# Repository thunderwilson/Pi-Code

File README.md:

prog_draft is a basic implementation of bluetooth scanning and data logging.

Takes a mock daily roster "daily.csv" (as per TANDA rostering) and works out who is working today.

It takes note of their start time and end time for use in the scanning algorithm (hence why the daily.csv only has the first 4 colums, the rest are ignored).

Currently the program just scans for everyone in the list at once and logs the changes in state in the corresponding *name*.csv file rather than using the start and finish times to decide when to scan. Thats this weeks job.

This file is then stored locally ready to be uploaded.

Currently using the bluetooth address of my phone and two fake addresses for testing. Only the Tom.csv file shows actual test data. Have ordered parts for the Bluetooth 'smart' badges which should arrive sometime next week. 

Running code on linux laptop which is setup the same as the Rasperry Pi (the Pi is not very powerful and would be a bitch to develop on).

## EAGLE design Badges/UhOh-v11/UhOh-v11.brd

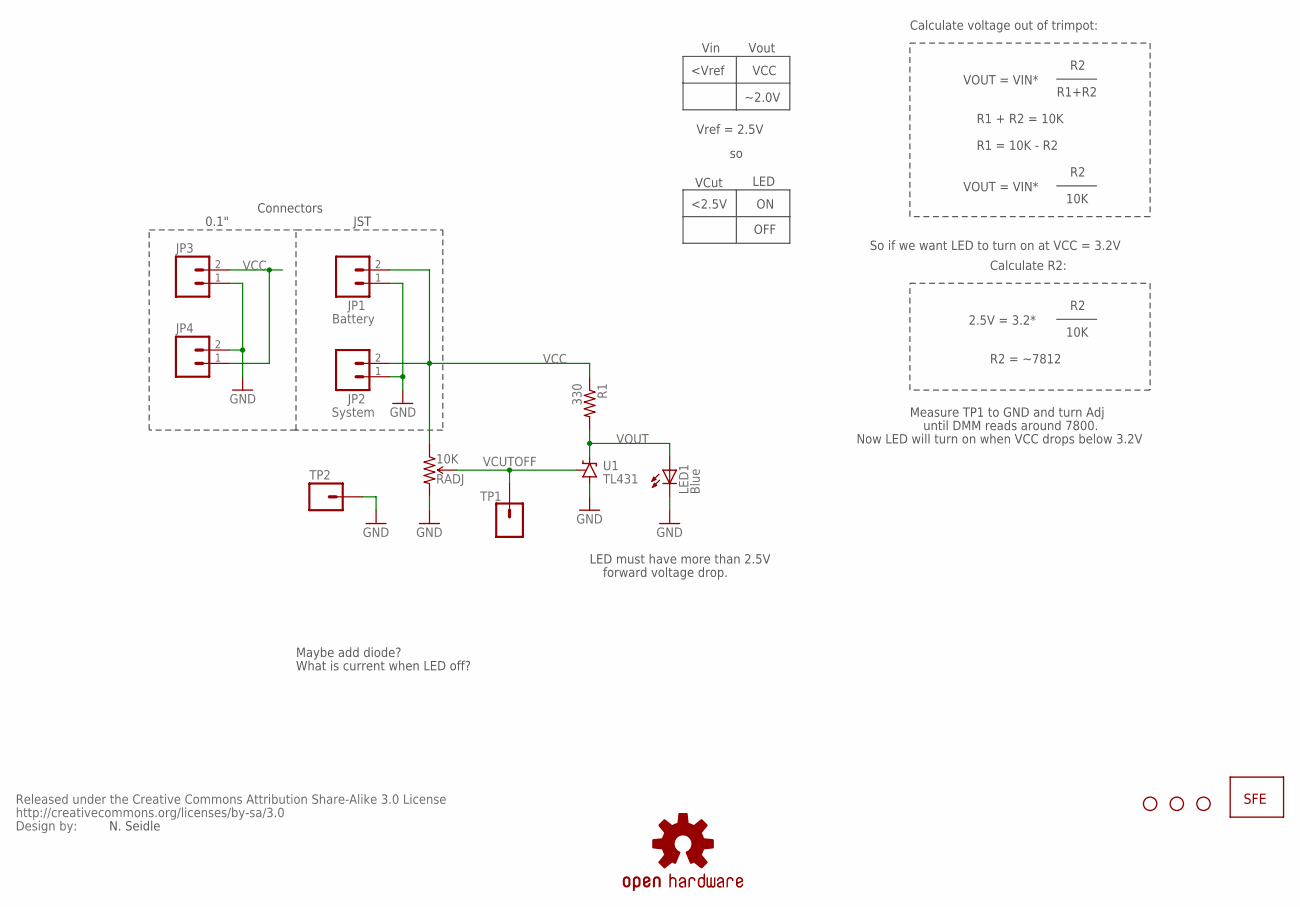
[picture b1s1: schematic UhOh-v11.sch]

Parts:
JP1: Battery; JST-2-PTH
JP2: System; JST-2-PTH
JP3, JP4: M02PTH; 1X02
JP31, JP41, JP61: STAND-OFF
JP51: LOGO-SFENEW; SFE-NEW-WEBLOGO
LED1: Blue; LED10MM-2
R1: 330; AXIAL-0.3
RADJ: 10K; 3386U
TP1: TP1; 1X01
TP2: TP2; 1X01
U1: TL431; TO-92
U$1: OSHW-LOGOS; OSHW-LOGO-S
U$2: CREATIVE_COMMONS

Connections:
GND: JP1.1, JP2.1, JP3.1, JP4.2, LED1.K (C), RADJ.3 (CW), TP2.1, U1.2 (A)
VCC: JP1.2, JP2.2, JP3.2, JP4.1, R1.P$1 (1), RADJ.1 (CCW)
VCUTOFF: RADJ.2 (WIPER), TP1.1, U1.1 (R)
VOUT: LED1.A, R1.P$2 (2), U1.3 (C)

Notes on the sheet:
N. Seidle
Connectors
0.1"
JST
Vref = 2.5V
Vin
Vout
<Vref
VCC
~2.0V
VOUT = VIN*
R1+R2
R1 + R2 = 10K
R1 = 10K - R2
10K
VCut
LED
<2.5V
OFF
So if we want LED to turn on at VCC = 3.2V
2.5V = 3.2*
Calculate voltage out of trimpot:
Calculate R2:
R2 = ~7812
Measure TP1 to GND and turn Adj
until DMM reads around 7800.
Now LED will turn on when VCC drops below 3.2V
LED must have more than 2.5V
forward voltage drop.
Maybe add diode?
What is current when LED off?

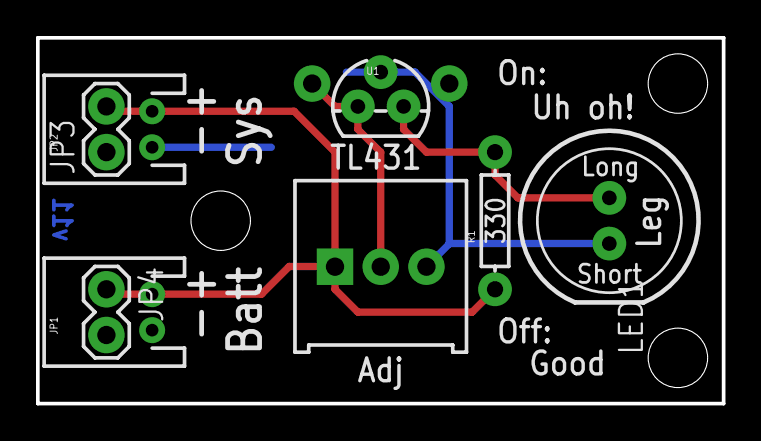
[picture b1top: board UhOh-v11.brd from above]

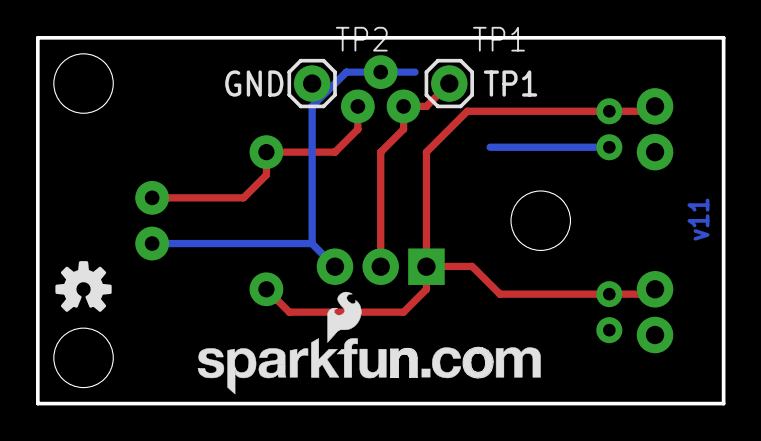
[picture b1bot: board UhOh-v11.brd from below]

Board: 2 copper layers, 38.1 x 20.3 mm, 16 parts (4 on the bottom side), 4 nets.

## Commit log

2014-11-18 Draft basic complete
2014-11-18 Basic Draft
2014-11-18 removed a bunch of old rubbish
2014-11-18 More Cleaning
2014-11-18 Removed old README
2014-11-18 Removed .pyc
2014-11-18 removed nmpa.py
2014-11-26 Two versions of draft
2014-12-02 Transitioning to BLE code
2014-12-04 Making it work on the Pi
2014-12-07 Adding Net Comms
2014-12-09 Differentiating server and client side code
2014-12-16 Added server
2014-12-16 Adding BLE setup script
2014-12-17 Adding some client side goodness
2015-01-12 Everything needs to be updated
2015-01-12 Old shit
2015-01-12 Oh cmon git
2015-01-12 Oh thank you senior chemistry
2015-01-12 Adding user.csv
2015-01-25 Removed some junk
2015-02-08 Random server side fixes

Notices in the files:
parts and their libraries:
SparkFun: Released under the Creative Commons Attribution Share-Alike 3.0 License
SparkFun: http://creativecommons.org/licenses/by-sa/3.0
